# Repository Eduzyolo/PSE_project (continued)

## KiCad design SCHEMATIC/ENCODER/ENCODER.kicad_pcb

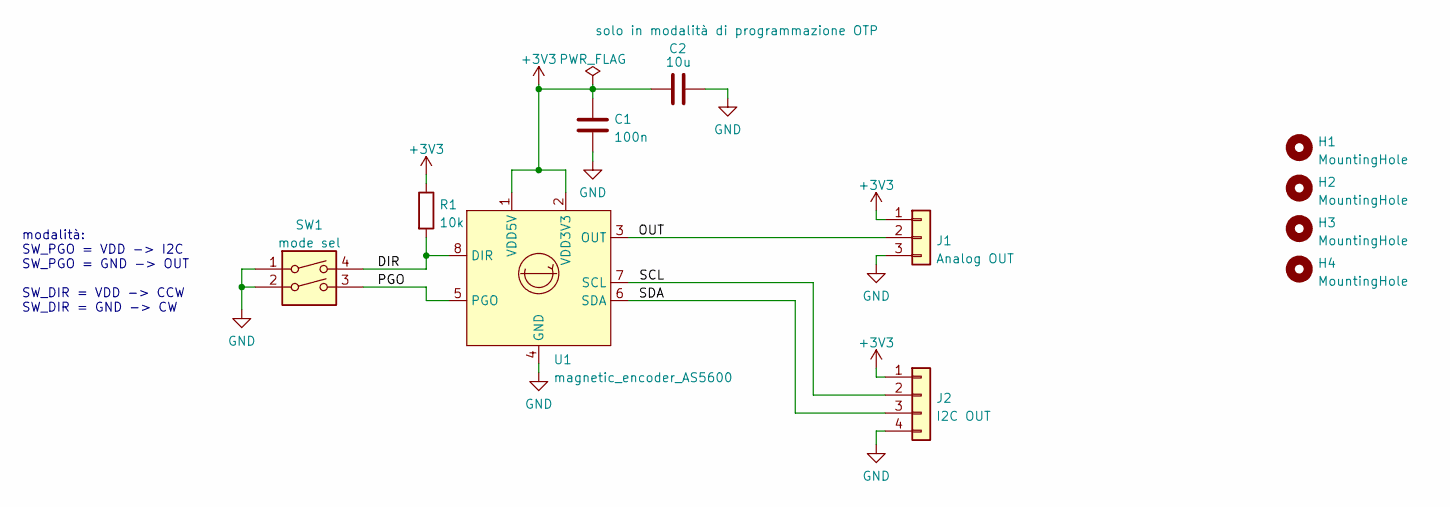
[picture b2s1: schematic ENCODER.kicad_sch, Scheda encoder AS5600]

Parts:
C1: 100n; C_0603_1608Metric
C2: 10u; PinSocket_1x02_P2.54mm_Vertical
H1, H2, H3, H4: MountingHole; MountingHole_3.2mm_M3_Pad_Via
J1: Analog OUT; JST_XH_B3B-XH-A_1x03_P2.50mm_Vertical
J2: I2C OUT; JST_XH_B4B-XH-A_1x04_P2.50mm_Vertical
R1: 10k; R_0603_1608Metric
SW1: mode sel; SW_DIP_SPSTx02_Slide_9.78x7.26mm_W7.62mm_P2.54mm; farnell 2864305
U1: magnetic_encoder_AS5600; SOIC-8_3.9x4.9mm_P1.27mm

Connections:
+3V3: C1.1, C2.1, J1.1, J2.1, R1.1, U1.1 (VDD5V), U1.2 (VDD3V3)
/DIR: R1.2, SW1.4, U1.8 (DIR)
/OUT: J1.2, U1.3 (OUT)
/PGO: SW1.3, U1.5 (PGO)
/SCL: J2.2, U1.7 (SCL)
/SDA: J2.3, U1.6 (SDA)
GND: C1.2, C2.2, J1.3, J2.4, SW1.1, SW1.2, U1.4 (GND)

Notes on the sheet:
modalità: SW_PGO = VDD -> I2C SW_PGO = GND -> OUT SW_DIR = VDD -> CCW SW_DIR = GND -> CW

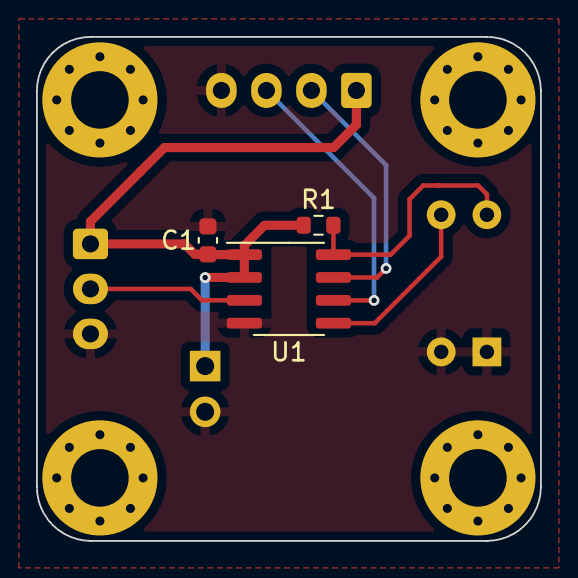
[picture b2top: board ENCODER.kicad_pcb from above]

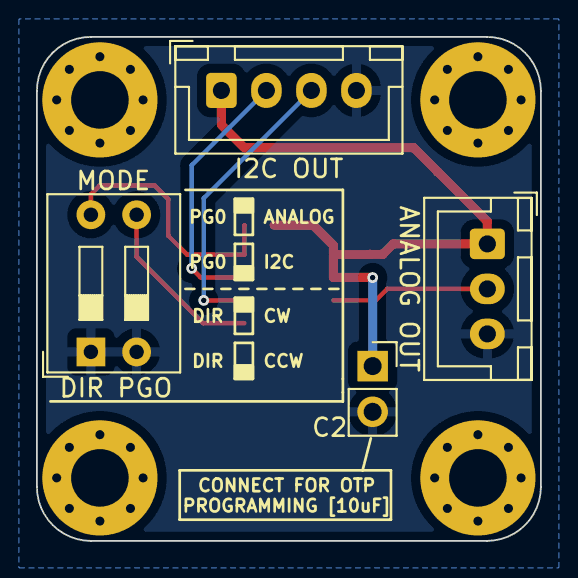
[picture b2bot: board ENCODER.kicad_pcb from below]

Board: 2 copper layers, 28.0 x 28.0 mm, 11 parts (4 on the bottom side), 7 nets.

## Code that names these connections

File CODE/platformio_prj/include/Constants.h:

#ifndef __DEFINES__
#define __DEFINES__

//GPIO Pin mapping   
#define LED_ALIVE 20 
#define LED_RP 25
#define LED_STRIP 13

#define SERIAL_BAUD_RATE 9600

#define SDA 0 
#define SCL 1 

#define USB_ID 2
#define USB_OUT_EN 27
#define WIFI_TX 17
#define WIFI_RX 16
#define WIFI_EN 3
#define UART_GPS_TX 4
#define UART_GPS_RX 5

#define BUTTON_UP 22
#define BUTTON_DOWN 23
#define BUTTON_RIGHT 24
#define BUTTON_LEFT 25
#define BUZZER 21

#define GPS_EN 18
#define GPS_PPS 19
#define GPS_RST 12

#define ACC_SA0 10
#define ACC_INT1 14
#define ACC_INT2 15

#define SERVO3 7
#define SERVO1 8
#define SERVO2 9

#define EN_5VOLT 11
//ANALOG INPUTS (ADC)
#define BATTERY_VOLTAGE 28
#define TEMPERAURE 26

//constants
#define SCREEN_WIDTH 128 // OLED display width, in pixels
#define SCREEN_HEIGHT 64 // OLED display height, in pixels
#define SCREEN_ADDRESS 0x3C //oled file to control it
#define NUM_PAGES 11 //number of pages in the oled screen tbd
#define EEPROM_ADDRESS 0x50 //hopefully, already defined in the library
#define ACC_ADDRESS 0x00
#define STRIP_LENGHT 8
#define AS5600_ADDRESS 0x36
#define TEMP_SENSOR_ADDRESS 0x48

// Define the I2C address of the MMA8451Q accelerometer
#define MMA8451Q_ADDR   0x1C

// Define the addresses of the MMA8451Q registers
#define MMA8451Q_CTRL_REG1      0x2A
#define MMA8451Q_OUT_X_MSB      0x01
#define MMA8451Q_OUT_Y_MSB      0x03
#define MMA8451Q_OUT_Z_MSB      0x05


enum Peripheral_state{
    MAIN_MENU,
    WIFI_SENDING,
    WIFI_RECEIVING,
    GPS_SENDING,
    ACC_SENDING,
    LEDS_DATA,
    TEMPERATURE_DATA,
    BATTERY_DATA,
    BUZZER_SIGNAL,
    PERIPHERAL_IDLE,
    PERIPHERAL_ERROR
};

#endif

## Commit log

2023-03-22 Fatto lo schema base
    Fatto lo schema base:
    - rp2040
    - buck
    - usb mini
    - flash...
2023-03-23 added empy project
2023-03-23 added pico examples as subomdule
2023-03-23 moved some files
2023-03-23 added pi pico examples with correct submodule path
2023-03-23 added CASE folder
2023-03-23 added libs for components
2023-03-25 aggiunto GPS, LED_alive, Buzzer, RGB_WS2812B
2023-03-28 Add files via upload
    aggiunto display, accelerometro, sensore temp
2023-03-28 Sistemato tutto lo schematico con fogli gerarchici
    Sistemato lo schematico, ordinato tutti i componenti nei vari fogli gerarchici.
    aggiunto ldo e sistemato il buck converter. aggiunti anche i terminali a vite per le connessioni esterne
2023-03-28 aggiunta memoria EEPROM a schematico
2023-03-29 sistemato tutto, e aggiunti i footprint da modificare
    sistemato tutto, aggiunto e modificato i footprint.
    Manca solo aggiungere i restanti footprint (praticamente solo dei componenti comuni)
2023-03-29 fatto schema e pcb scheda encoder
2023-03-30 prova librerie
2023-03-30 caricati anche i modelli 3d
2023-03-30 added ino testing
2023-03-30 removed pico test
2023-03-30 added rickroll
2023-03-30 Aggiunti QUASI tutti i footprint
    aggiunti quasi tutti i footprint dei componenti
2023-03-30 added ifdef macro
2023-04-01 Aggiunto Modello 3d case ENCODER
2023-04-04 iniziato il layout, posizionati componenti principali
    incominciato il posizionamento dei componenti nel layout. Sono stati posizionati i componenti principali come led RGB, GPS, schermo, pulsanti vari, buzzer
2023-04-05 Posizionati tutti i componenti
    Posizionati tutti i componenti sulla scheda
2023-04-13 iniziato lo broglio. Prima di continuare modificare pin schema
    iniziato lo sbroglio della scheda, prima di continuare bisogna sistemare i pin che siano concordi con quelli degli altro (ovvero sistemarli come da tabella su telegram)
2023-04-14 sistemato buzzer, e continuato lo sbroglio
    sistemato il buzzer con un altro footprint e ho continuato lo sbroglio.
    Teoricamente manca solo collegare i collegamenti tra le gpio del rp2040 e il resto dei componenti
2023-04-14 modificato pin 2,3,14,15,16,17,18,27,28,29,30,31,32
2023-04-14 finito lo sbroglio (magari da ricontrollare)
    finito lo sbroglio, controllato già io ma meglio ridare una controllata.
    Da sistemare tutta la serigrafia
2023-04-15 finito tutto
    sistemati tutti i nomi dei componenti e inserite tutte le grafiche necessarie
2023-04-15 sistemato nomi periferiche esterne uart e i2c
2023-04-17 abbellita un po' la scheda
    sostituite alcune scritte sulla sceda
2023-04-17 cambiati i pulsanti in smd
    se servono gli altri pulsanti usare la versione precedente
2023-04-17 Aggiunte tutte le cose richieste dal prof
    Aggiunte tutte le cose richieste dal prof:
    wifi
    servo
    uscita led
    MANCA DA METERE IL SOLDER MASK SUI PAD NON USATI DEL GPS
2023-04-18 Sistemate un po'di cose
    aggiuno fori display e terzo servo e sistemate le serigrafie
2023-04-19 Aggiunto mosfet uscita corrente usb
    Ultima modifica prima della revisone generale.
    aggiunto un mosfet P per l'attivazione dell'uscita della tensione alla usb in caso di master
2023-04-20 Versione definitiva inviata ai prof
    Sistemato tutto e inviato il tutto ai prof
2023-05-04 added test test code
2023-05-04 added accelerometer test
2023-05-04 added oled test
2023-05-04 added test gps
2023-05-05 moved files to another folder
2023-05-09 last version arduino
2023-05-09 moved to platformio
2023-05-09 added eeprom
2023-05-13 aggiunto file modello 3d encoder
    aggiunte istruzioni e materiali necessari sul file README
2023-05-20 added test code for encoder
2023-05-20 added luca submodule
2023-05-21 test temperature
2023-05-21 added buttons test
2023-05-21 fixes and added constans
2023-05-22 updated encoder code
2023-05-22 mionr changes
2023-06-15 creato case scheda
    creato case scheda e fatto qualche render
2023-06-18 finito il case e aggiunti file per la stampa 3d
2023-06-18 sistemato qualche file per la stampa 3d
2023-06-22 modificato qualche modello 3d del case
2023-06-27 mmionr changes
2023-06-27 basic stuff added
2023-06-27 second version of basic distance
2023-11-29 Create LICENSE
